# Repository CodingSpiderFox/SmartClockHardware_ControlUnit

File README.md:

# SmartClockHardware (ControlUnit)

This is part of the the hardware specification for my smart clock project.

The hardware consists of one device for the wake-up light functionality and another for the controls and LCD display.

The control unit with the display again, consists of 3 major parts held in one encasing

1.1) The controller for the input devices: various buttons and a PIR motion sensor.
There are many buttons for quite a lot of different features. As the NodeMCU doesn't have enough pins, two PCF8574 IO expander chips are used (yes, I tried the MCP23017 but didn't like the libraries and didn't want to write a new one).

1.2) The Mega2560 devboard with a 2.8" touch display shield on it and the two other parts (1.1 and 1.3) connected via hardware serials.

1.3) The NodeMCU controlling the illuminated button's lights.
Two buttons have RGB leds in the which can be controlled separately.
The other 9 buttons have single colour LEDs. All of the button's LEDs can be adjusted to different brightness levels, together with the LCD panel's backlight brightness.

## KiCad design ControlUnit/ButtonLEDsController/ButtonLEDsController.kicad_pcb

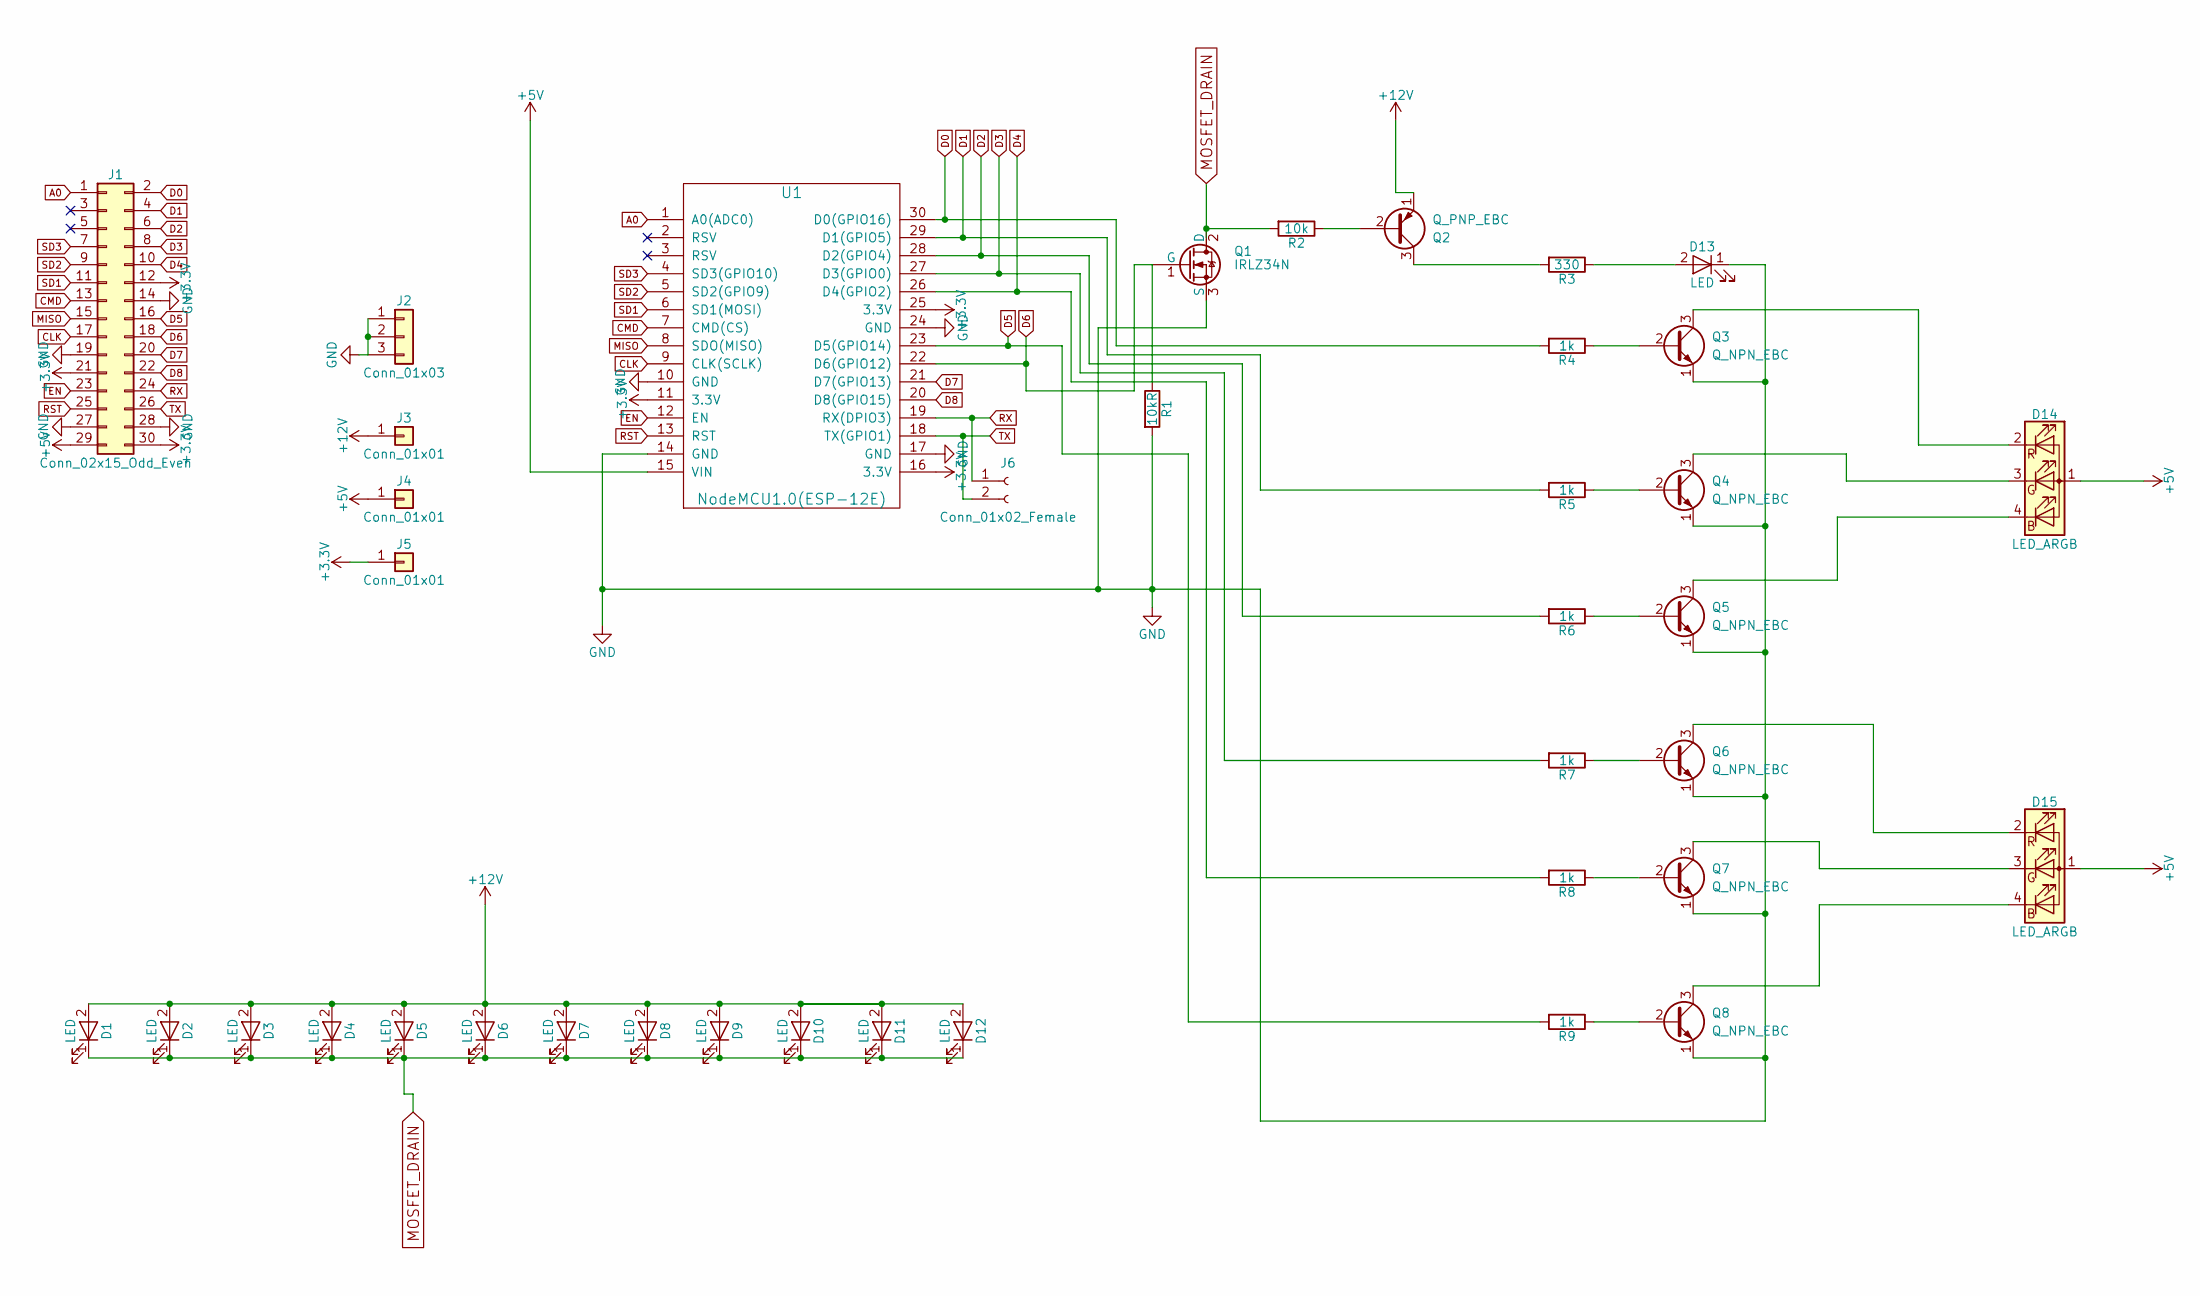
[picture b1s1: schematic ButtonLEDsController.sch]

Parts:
D1, D2, D3, D4, D5, D6, D7, D8, D9, D10, D11, D12, D13: LED; LED_D5.0mm
D14, D15: LED_ARGB; Pin_Header_Straight_1x04
J1: Conn_02x15_Odd_Even; Pin_Header_Straight_2x15_Pitch2.54mm
J2: Conn_01x03; Pin_Header_Straight_1x03_Pitch2.54mm
J3, J4, J5: Conn_01x01; Pin_Header_Straight_1x01_Pitch2.54mm
J6: Conn_01x02_Female; Socket_Strip_Straight_1x02_Pitch2.54mm
Q1: IRLZ34N; TO-220
Q2: Q_PNP_EBC; TO-92_Molded_Narrow
Q3, Q4, Q5, Q6, Q7, Q8: Q_NPN_EBC; TO-92_Molded_Narrow
R1: 10kR; R_Axial_DIN0204_L3.6mm_D1.6mm_P7.62mm_Horizontal
R2: 10k; R_Axial_DIN0204_L3.6mm_D1.6mm_P7.62mm_Horizontal
R3: 330; R_Axial_DIN0204_L3.6mm_D1.6mm_P7.62mm_Horizontal
R4, R5, R6, R7, R8, R9: 1k; R_Axial_DIN0204_L3.6mm_D1.6mm_P7.62mm_Horizontal
U1: NodeMCU1.0(ESP-12E); NodeMCU1.0(12-E)

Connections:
+3V3: J1.12, J1.21, J1.30, J5.1, U1.11 (3.3V), U1.16 (3.3V), U1.25 (3.3V)
+5V: D14.1 (A), D15.1 (A), J1.29, J4.1, U1.15 (VIN)
+12V: D1.2 (A), D2.2 (A), D3.2 (A), D4.2 (A), D5.2 (A), D6.2 (A), D7.2 (A), D8.2 (A), D9.2 (A), D10.2 (A), D11.2 (A), D12.2 (A), J3.1, Q2.1 (E)
A0: J1.1, U1.1 (A0(ADC0))
CLK: J1.17, U1.9 (CLK(SCLK))
CMD: J1.13, U1.7 (CMD(CS))
D0: J1.2, R4.2, U1.30 (D0(GPIO16))
D1: J1.4, R5.2, U1.29 (D1(GPIO5))
D2: J1.6, R6.2, U1.28 (D2(GPIO4))
D3: J1.8, R7.2, U1.27 (D3(GPIO0))
D4: J1.10, R8.2, U1.26 (D4(GPIO2))
D5: J1.16, R9.2, U1.23 (D5(GPIO14))
D6: J1.18, Q1.1 (G), R1.1, U1.22 (D6(GPIO12))
D7: J1.20, U1.21 (D7(GPIO13))
D8: J1.22, U1.20 (D8(GPIO15))
EN: J1.23, U1.12 (EN)
GND: D13.1 (K), J1.14, J1.19, J1.27, J1.28, J2.1, J2.2, J2.3, Q1.3 (S), Q3.1 (E), Q4.1 (E), Q5.1 (E), Q6.1 (E), Q7.1 (E), Q8.1 (E), R1.2, U1.10 (GND), U1.14 (GND), U1.17 (GND), U1.24 (GND)
MISO: J1.15, U1.8 (SDO(MISO))
MOSFET_DRAIN: D1.1 (K), D2.1 (K), D3.1 (K), D4.1 (K), D5.1 (K), D6.1 (K), D7.1 (K), D8.1 (K), D9.1 (K), D10.1 (K), D11.1 (K), D12.1 (K), Q1.2 (D), R2.2
unnamed: D13.2 (A), R3.1
unnamed: D14.2 (RK), Q3.3 (C)
unnamed: D14.3 (GK), Q4.3 (C)
unnamed: D14.4 (BK), Q5.3 (C)
unnamed: D15.2 (RK), Q6.3 (C)
unnamed: D15.3 (GK), Q7.3 (C)
unnamed: D15.4 (BK), Q8.3 (C)
unnamed: Q2.2 (B), R2.1
unnamed: Q2.3 (C), R3.2
unnamed: Q3.2 (B), R4.1
unnamed: Q4.2 (B), R5.1
unnamed: Q5.2 (B), R6.1
unnamed: Q6.2 (B), R7.1
unnamed: Q7.2 (B), R8.1
unnamed: Q8.2 (B), R9.1
RST: J1.25, U1.13 (RST)
RX: J1.24, J6.1, U1.19 (RX(DPIO3))
SD1: J1.11, U1.6 (SD1(MOSI))
SD2: J1.9, U1.5 (SD2(GPIO9))
SD3: J1.7, U1.4 (SD3(GPIO10))
TX: J1.26, J6.2, U1.18 (TX(GPIO1))

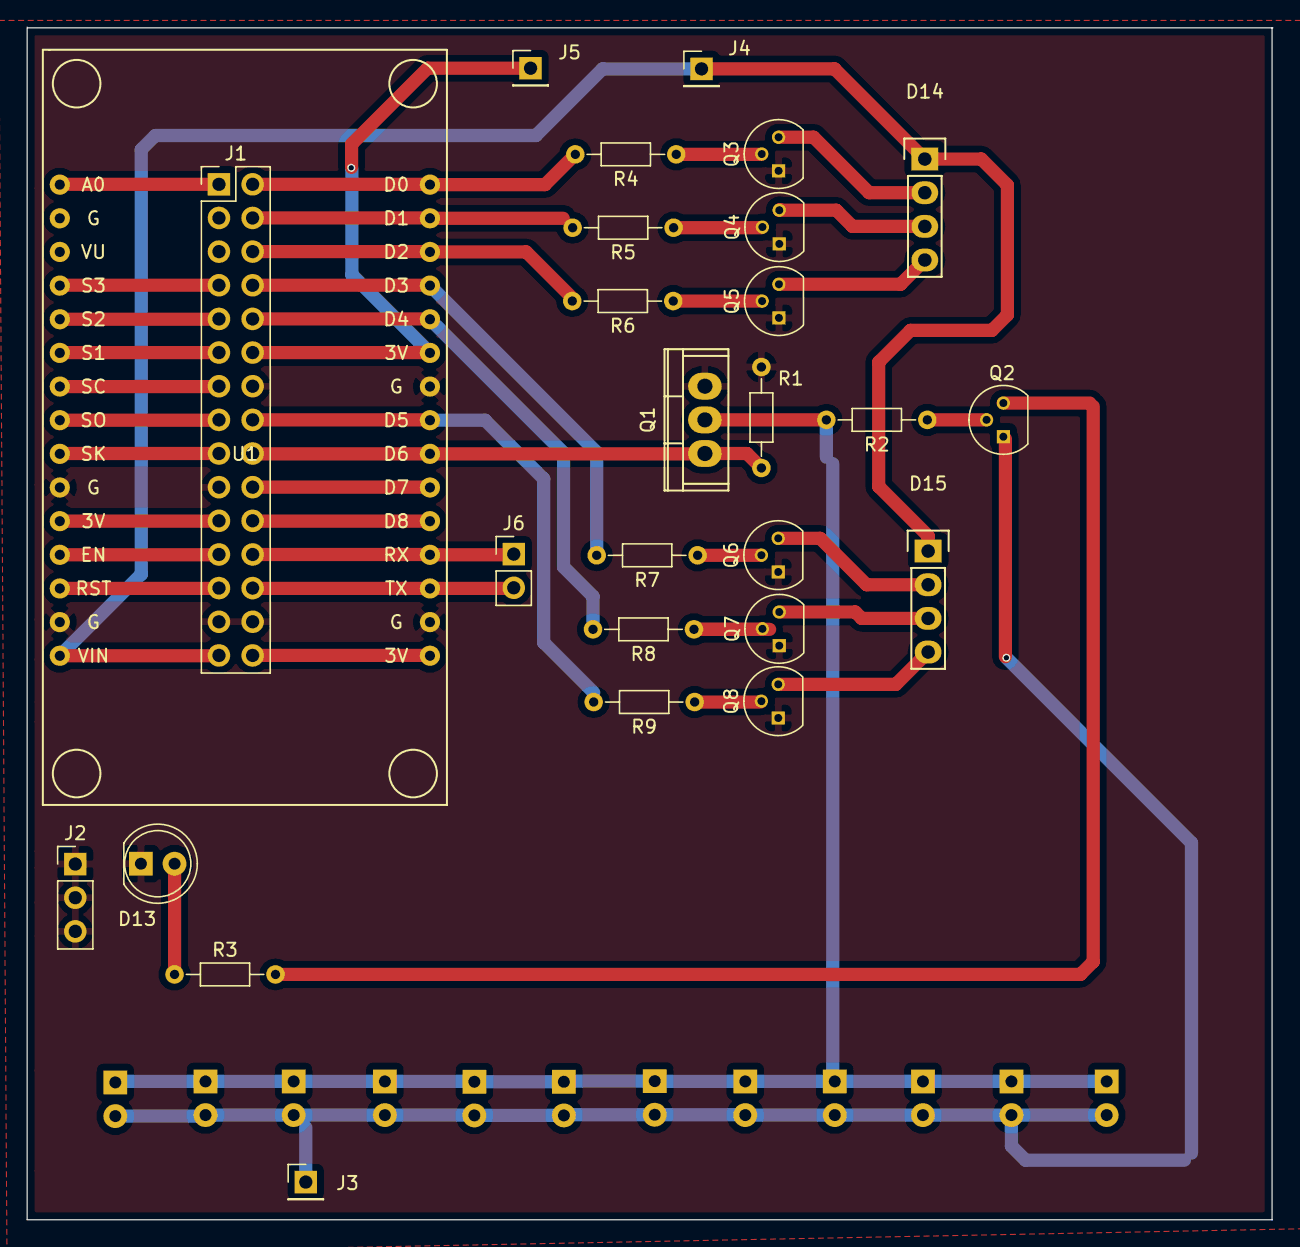
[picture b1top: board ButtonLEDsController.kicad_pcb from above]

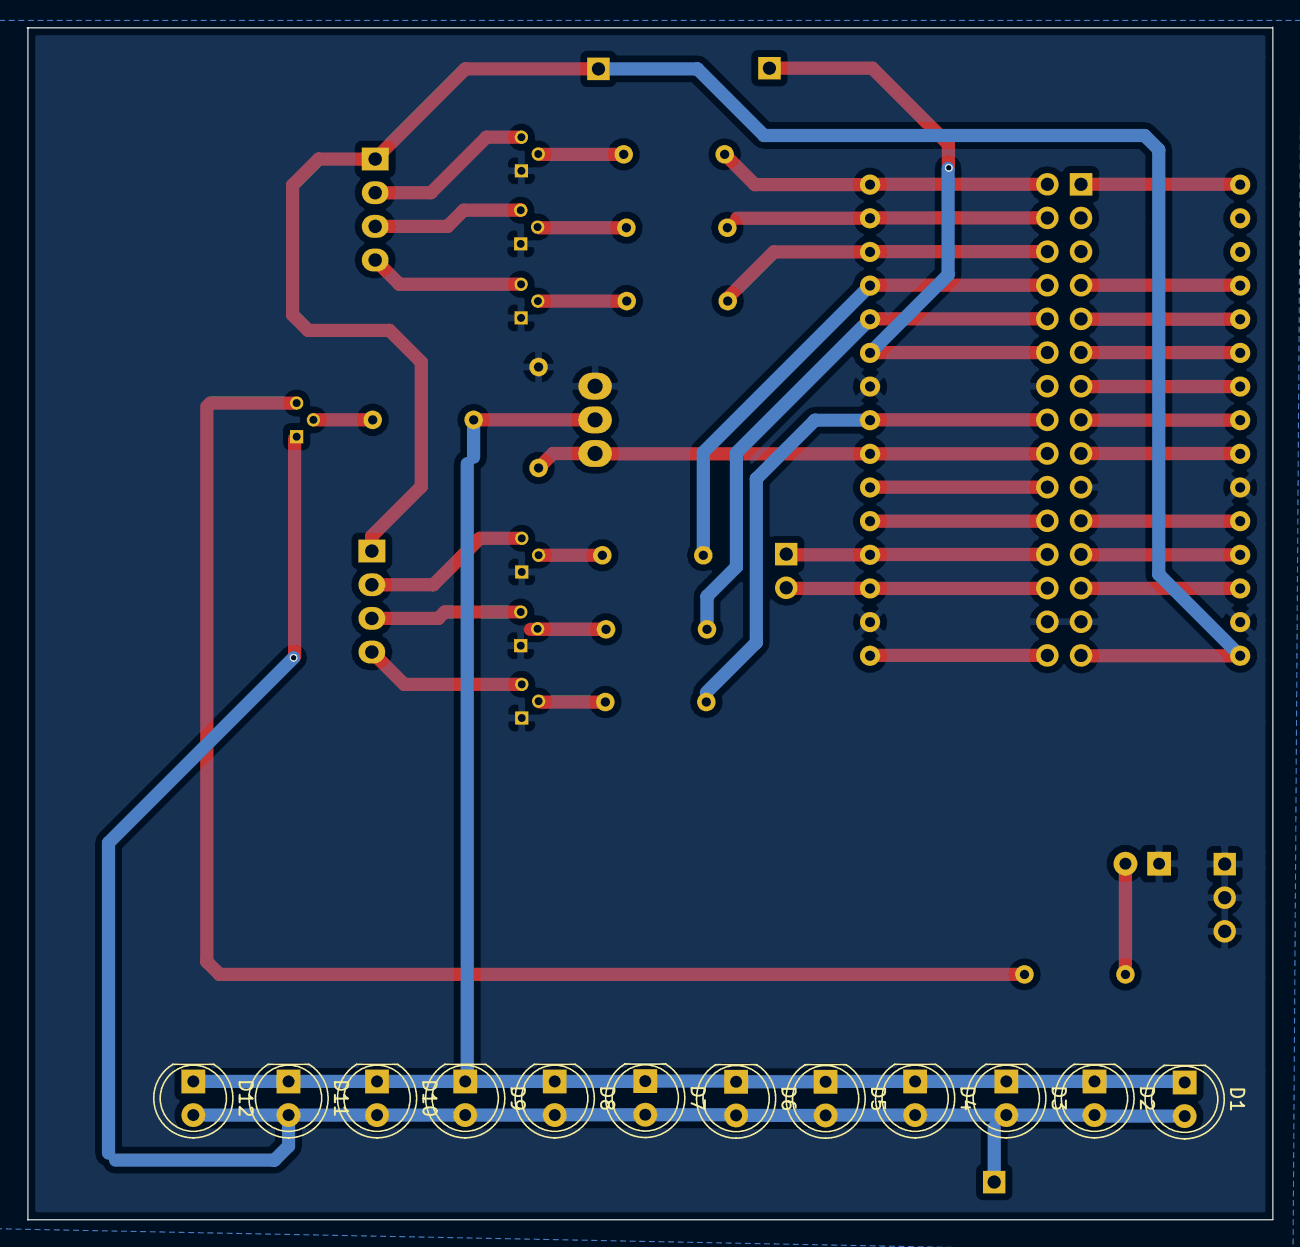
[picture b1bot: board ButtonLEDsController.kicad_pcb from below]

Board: 2 copper layers, 94.0 x 90.0 mm, 39 parts (12 on the bottom side), 40 nets.

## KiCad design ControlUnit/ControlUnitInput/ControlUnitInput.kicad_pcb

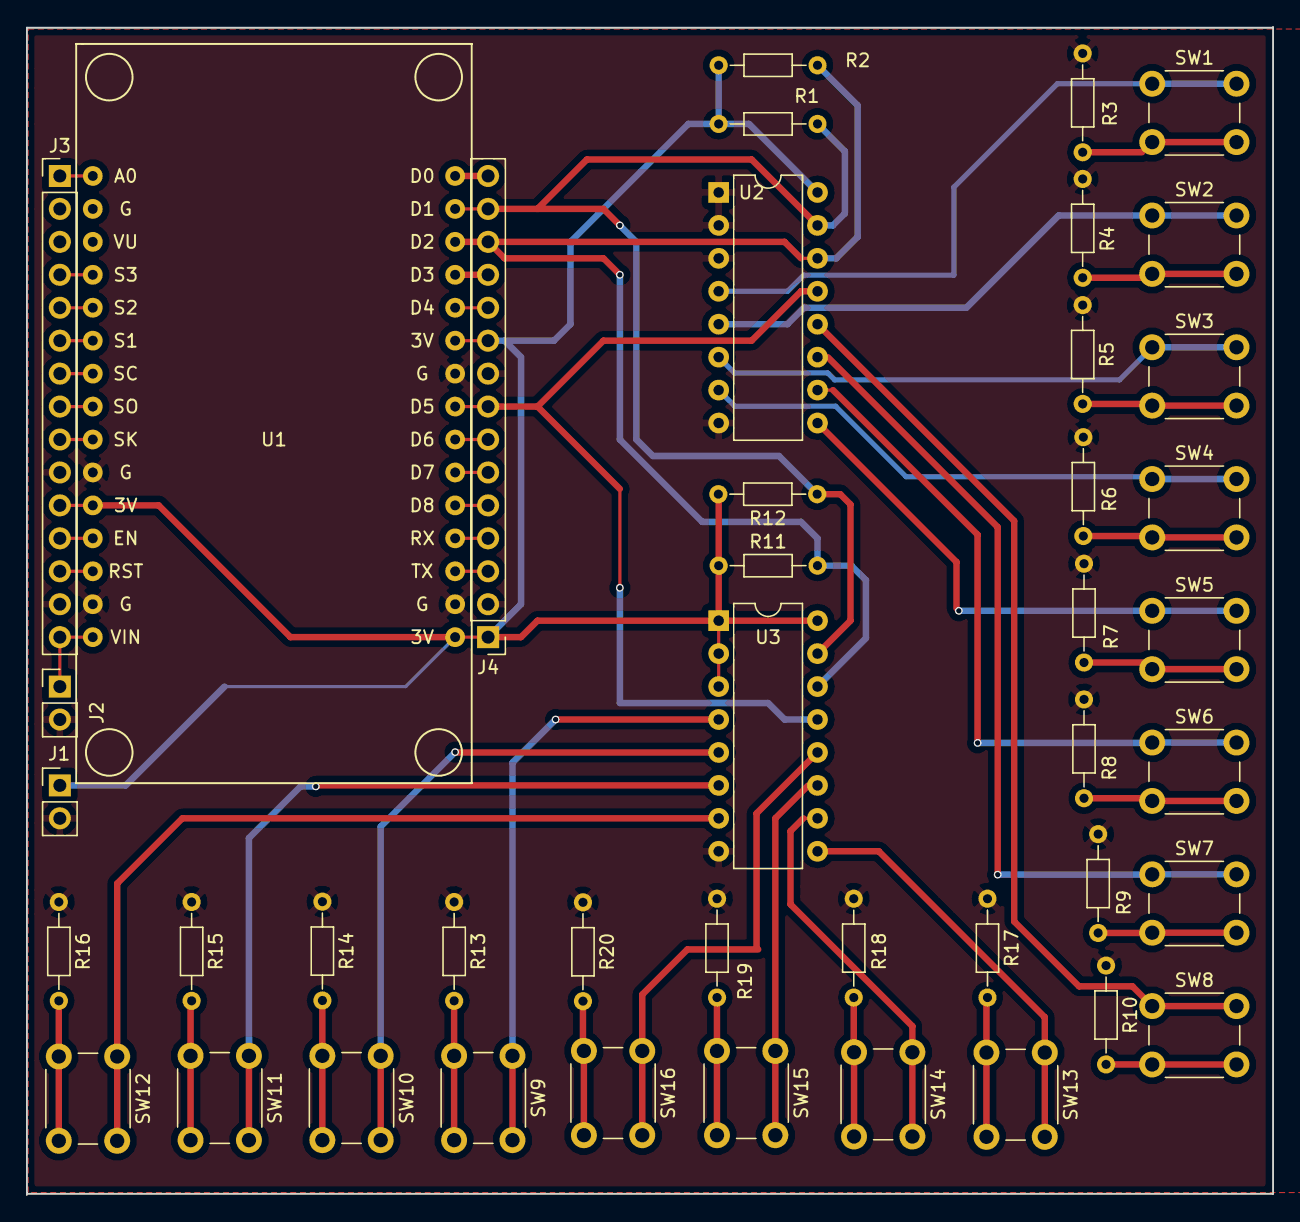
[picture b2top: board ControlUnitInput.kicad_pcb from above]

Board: 2 copper layers, 96.1 x 90.1 mm, 43 parts (0 on the bottom side), 55 nets.

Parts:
J1, J2: Pin_Header_Straight_1x02_Pitch2.54mm
J3, J4: Pin_Header_Straight_1x15_Pitch2.54mm
R1, R2, R11, R12: 4.7k; R_Axial_DIN0204_L3.6mm_D1.6mm_P7.62mm_Horizontal
R3, R4, R5, R6, R7, R8, R9, R10, R13, R14, R15, R16, R17, R18, R19, R20: 10k; R_Axial_DIN0204_L3.6mm_D1.6mm_P7.62mm_Horizontal
SW1, SW2, SW3, SW4, SW5, SW6, SW7, SW8, SW9, SW10, SW11, SW13, SW14, SW15, SW16: SW_Push; SW_PUSH_6mm_h8mm
SW12: SW_PUSH_6mm_h8mm
U1: NodeMCU1.0(ESP-12E); NodeMCU1.0(12-E)
U2: DIP-16_W7.62mm
U3: PCF8574; DIP-16_W7.62mm

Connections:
+3V3: J1.1, J3.11, J4.1, J4.10, R1.2, R2.1, R11.1, R12.2, U1.11, U1.16, U1.25, U2.16, U3.1, U3.2, U3.3, U3.16
+5V: J2.1, J3.15, U1.15
A0: J3.1, U1.1
CLK: J3.9, U1.9
CMD: J3.7, U1.7
D0: J4.15, U1.30
D3: J4.12, U1.27
D4: J4.11, U1.26
D6: J4.7, U1.22
D7: J4.6, U1.21
D8: J4.5, U1.20
EN: J3.12, U1.12
GND: J1.2, J2.2, J3.10, J3.14, J4.2, J4.9, R3.1, R4.1, R5.1, R6.1, R7.1, R8.1, R9.1, R10.1, R13.1, R14.1, R15.1, R16.1, R17.1, R18.1, R19.1, R20.1, U1.10, U1.14, U1.17, U1.24, U2.1, U2.2, U2.3, U2.8, U3.8
INT: J4.8, U1.23, U2.13, U3.13
MISO: J3.8, U1.8
MOSI: J3.6, U1.6
unnamed: R3.2, SW1.2
unnamed: R4.2, SW2.2
unnamed: R5.2, SW3.2
unnamed: R6.2, SW4.2
unnamed: R7.2, SW5.2
unnamed: R8.2, SW6.2
unnamed: R9.2, SW7.2
unnamed: R10.2, SW8.2
unnamed: R13.2, SW9.2
unnamed: R14.2, SW10.2
unnamed: R15.2, SW11.2
unnamed: R16.2, SW12.2
unnamed: R17.2, SW13.2
unnamed: R18.2, SW14.2
unnamed: R19.2, SW15.2
unnamed: R20.2, SW16.2
unnamed: SW1.1, U2.4
unnamed: SW2.1, U2.5
unnamed: SW3.1, U2.6
unnamed: SW4.1, U2.7
unnamed: SW5.1, U2.9
unnamed: SW6.1, U2.10
unnamed: SW7.1, U2.11
unnamed: SW8.1, U2.12
unnamed: SW9.1, U3.4
unnamed: SW10.1, U3.5
unnamed: SW11.1, U3.6
unnamed: SW12.1, U3.7
unnamed: SW13.1, U3.9
unnamed: SW14.1, U3.10
unnamed: SW15.1, U3.11
unnamed: SW16.1, U3.12
RST: J3.13, U1.13
RX: J4.4, U1.19
SCL: J4.13, R2.2, R11.2, U1.28, U2.14, U3.14
SD2: J3.5, U1.5
SD3: J3.4, U1.4
SDA: J4.14, R1.1, R12.1, U1.29, U2.15, U3.15
TX: J4.3, U1.18

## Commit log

2018-10-13 1mm thickness for all tacks
2018-10-13 0.4 - 0.5 mm track thickness
2018-11-05 prepared to order pcbs

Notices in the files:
ControlUnit/ButtonLEDsController/ButtonLEDsController.kicad_pcb:
License: CERN OHL v1.2
